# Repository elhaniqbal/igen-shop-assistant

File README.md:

<div align="center">

# HAVEN

**Automated tool dispensing and return kiosk — UBC IGEN 430 Capstone**

</div>

---

A student taps their UBC card, selects tools on a touchscreen kiosk, and the machine retrieves them — a gantry positions itself over the right carousel, rotates it to the target slot, and presents the tool at the door. Returns work in reverse. The system tracks loans, flags overdues, and sends email alerts. Everything runs in Docker on a Raspberry Pi.

This is a capstone demo. It runs end-to-end on real hardware and was built with production in mind from the start — the session mechanism, schema, network isolation, and service topology are all production-quality decisions. Getting it the rest of the way is a set of specific, well-scoped additions, not a rewrite. More on that [below](#getting-to-production).

---

## Demo

<div align="center">
  
  <br/><sub>▶ Click to watch on YouTube</sub>
</div>

---

## Architecture

```
┌──────────────────────────────────────────────────────────┐
│                 Raspberry Pi (Docker Compose)             │
│                                                          │
│  React Kiosk ──── HTTP polling ────► FastAPI Backend     │
│  (Nginx :8080)                       (Uvicorn :8000)     │
│                                      SQLite/SQLAlchemy   │
│                                            │             │
│                                       MQTT pub/sub       │
│                                            │             │
│                                  Eclipse Mosquitto       │
│                                   (1883 / WS:9001)       │
│                                            │             │
│                              ┌─────────────┴──────────┐  │
│                         Bridge sidecar      RFID sidecar │
│                         (bridge.py)        (rfid_service)│
│                              │                   │       │
└──────────────────────────────┼───────────────────┼───────┘
                               │ HTTP              │ SPI/GPIO
                        Moonraker API         MFRC522 reader
                        (:7125)
                               │ G-code macros
                            Klipper
                               │
                      BTT Octopus MAX EZ
                               │
              gantry1 / gantry2 / horiz / cake steppers
```

The frontend never touches hardware directly. It polls the backend over HTTP; the backend fires MQTT commands; the bridge translates those into Klipper G-code macros via Moonraker's HTTP API. Klipper handles all stepper control on the BTT Octopus board.

The bridge runs in one of two modes set via `BRIDGE_MODE`:
- `MOONRAKER` — real hardware via Moonraker's HTTP API
- `SIM` — software simulation with configurable timing and fail rate, no physical machine required

---

## Hardware

**Stepper axes**

- `horiz` — horizontal axis, positions the gantry over a carousel
- `gantry1`, `gantry2` — dual independent vertical axes, lifts tools in and out of slots
- `cake0`–`cake5` — one stepper per carousel, 60° per slot step

Each carousel ("cake") has 6 slots. The gantry moves horizontally to the target carousel, the vertical axes lower, the carousel rotates to the right slot, and the tool is picked up or deposited.

Vertical homing can't use Klipper's native `G28` because both gantry sides need to find their endstops independently. `vertical_home.py` handles this by jogging each side in 1600-step increments and polling Moonraker's endstop API until both trigger, then zeroing both steppers.

**Klipper macros (selected)**

```
SA_MOVE_TO_CAKE CAKE=<n>              position gantry over carousel n
SA_ROTATE_TO_SLOT CAKE=<n> SLOT=<s>   rotate carousel to absolute slot
MOVE_CAKE_CW_60 CAKE=<n>              rotate one slot clockwise
MOVE_CAKE_CCW_60 CAKE=<n>             rotate one slot counter-clockwise
SA_ROTATE_TO_DISPENSE CAKE=<n>        final alignment to dispense window
SA_MOVE_TO_DOOR                       extend gantry to door position
SA_PARK                               return to home/park
SA_HOME_HORIZONTAL                    home horizontal axis
SA_JOG_GANTRY_UP/DOWN DIST=<n>        manual jog (admin)
```

**Custom PCB — Encoder multiplexer**

<div align="center">

</div>

Each carousel has an AS5600 magnetic absolute encoder. Since all AS5600s share I2C address `0x36`, a TCA9548A multiplexer switches between them. An ESP32 reads all six, persists per-carousel zero offsets to EEPROM, and exposes a simple serial command interface.

When `ENCODER_SERIAL_ENABLED=1`, the bridge reads the angle before and after each carousel rotation and fires an alert if the measured delta is outside tolerance. Mismatches are logged and surfaced in the admin panel — it's a sanity check, not a safety gate; the operation still completes.

**NFC student card**

<div align="center">

</div>

The authentication card is a custom PCB — originally a personal side project to build a business-card-sized NFC tag. It turned out to be directly useful here: it's ISO 14443 compliant, so the MFRC522 reads it identically to any standard card. No firmware changes were needed.

---

## Sequence diagrams

<table>
<tr>
<td align="center">

<br/><sub>Dispense</sub>
</td>
<td align="center">

<br/><sub>Return</sub>
</td>
</tr>
</table>

Full diagrams with per-stage MQTT events and Moonraker calls: [`docs/system-overview.md`](docs/system-overview.md)

---

## Screenshots

<table>
<tr>
<td align="center"><br/><sub>Admin panel — manual gantry and carousel control</sub></td>
<td align="center"><br/><sub>Carousel slot state view</sub></td>
</tr>
</table>

---

## Poster

<div align="center">

</div>

---

## Stack

| | |
|---|---|
| Frontend | React 18, TypeScript, Vite, Tailwind CSS |
| Backend | Python 3.11, FastAPI, SQLAlchemy 2.0, Pydantic |
| Messaging | Eclipse Mosquitto 2, Paho |
| Database | SQLite (WAL mode) |
| Motion control | Klipper, Moonraker HTTP API |
| Firmware | Arduino/PlatformIO, ESP32, AS5600, TCA9548A |
| Infrastructure | Docker Compose, Nginx |
| Notifications | SendGrid |
| Hardware | BTT Octopus MAX EX, MFRC522 RFID, NEMA steppers |

---

## Getting started

**Prerequisites:** Docker, Docker Compose, Git

### 1. Clone and configure

```bash
git clone https://github.com/elhaniqbal/igen-shop-assistant.git
cd igen-shop-assistant
```

Create a `.env` in the repo root. Minimum to run without hardware:

```env
DATABASE_URL=sqlite:////app/data/igen.db
MQTT_BROKER=mqtt
MQTT_PORT=1883

# SIM runs without any physical hardware attached
BRIDGE_MODE=SIM

# Set to 1 to mock RFID scans in the browser
VITE_MOCK=1

# Only used in MOONRAKER mode
MOONRAKER_URL=http://host.docker.internal:7125

SENDGRID_API_KEY=
SENDGRID_FROM_EMAIL=
```

### 2. Build and start

```bash
docker compose up --build
```

| Service | URL |
|---|---|
| Kiosk | http://localhost:8080 |
| Backend API | http://localhost:5000 |
| MQTT Web UI | http://localhost:8090 |
| DB Admin | http://localhost:8083 |

The database is created automatically at `./data/igen.db` on first run.

> `5000:8000` is a dev convenience. In production, remove the port mapping — the backend is already on the `internal` Docker network and Nginx proxies it. Nothing outside the host should reach port 8000 directly.

### 3. Create the first admin user

There's no seed data. `POST /api/admin/users` has no auth guard (see [rough edges](#rough-edges)), so you can bootstrap directly:

```bash
curl -s -X POST http://localhost:5000/api/admin/users \
  -H "Content-Type: application/json" \
  -d '{
    "first_name": "Admin",
    "last_name": "User",
    "role": "admin",
    "status": "active",
    "card_id": "your-rfid-card-uid"
  }'
```

If you don't have your card UID yet, omit `card_id` and patch it in after scanning. The interactive API docs at `http://localhost:5000/docs` work for this too.

### 4. Seed inventory

Before anything can be dispensed, you need:
- **Tool models** (`POST /api/admin/tool-models`) — tool type, name, max loan hours, max quantity per user
- **Tool items** (`POST /api/admin/tool-items`) — links a physical item to a model, assigns it to a carousel slot, and registers its RFID tag

### Running against real hardware

Set `BRIDGE_MODE=MOONRAKER` and point `MOONRAKER_URL` at your Moonraker instance. The RFID sidecar needs SPI/GPIO access to the MFRC522 — the relevant device mounts are in `docker-compose.yaml`, just uncomment them.

Crowsnest (Klipper camera streaming) runs as a system service on the Pi, not in Docker. Set its port to `8091` to avoid conflicting with the kiosk on `8080`:

```conf
# /home/pi/printer_data/config/crowsnest.conf
[cam 1]
mode: ustreamer
port: 8091
device: /dev/v4l/by-id/usb-ARDUCAM_<your-camera>-video-index0
resolution: 1280x720
max_fps: 20
```

### Remote access via Tailscale

[Tailscale](https://tailscale.com) is what we use for remote access. `tailscale serve` proxies a local port to your tailnet over HTTPS; `tailscale funnel` makes it publicly reachable.

Tailnet-only (recommended for admin tools):

```bash
tailscale serve --bg http://localhost:8080          # kiosk
tailscale serve --bg --tcp 8090 tcp://localhost:8090  # MQTT Web UI
tailscale serve --bg --tcp 8083 tcp://localhost:8083  # DB Admin
tailscale serve --bg --tcp 8091 tcp://localhost:8091  # Crowsnest camera
```

Public via Funnel (for a live demo):

```bash
tailscale serve --bg http://localhost:8080
tailscale funnel --bg 443
```

Keep the MQTT broker (1883), Moonraker (7125), and the raw backend (5000) off Tailscale — none of them have auth.

---

## Rough edges

The architecture was designed with production in mind — network isolation, PostgreSQL-compatible schema, cryptographically secure sessions with revocation and role enforcement are all there. These are the specific gaps that didn't get closed before the demo:

- **Admin routes have no auth guard.** `require_admin_user()` is fully implemented in `auth.py` — it just isn't applied to the `/api/admin/*` routes yet. Anything that can reach port 5000 can create users, modify loans, or trigger hardware. Network isolation protected it for the demo.
- **No password-based admin login.** Sessions are issued after an RFID card scan — the kiosk flow is solid. There's no separate credential login for the admin web panel; access is by network position and role field.
- **Klipper positions are in step units, not millimeters.** `rotation_distance` was never configured on the `MANUAL_STEPPER` definitions. Calibration is empirical; the position numbers in the admin panel are meaningless without knowing the motor specs.
- **No crash recovery for in-progress hardware ops.** If the bridge crashes mid-dispense, `loan_requests.hw_status` stays `in_progress` and the machine's physical state is unknown. Recovery is manual: rehome, update the DB.
- **Door timeout creates unconfirmed loans.** The bridge waits 20s (`DOOR_CONFIRM_TIMEOUT_S`) for the user to confirm they've taken the tool. On timeout it marks the dispense as complete — the loan is created without `confirmed_at`.
- **Encoder mismatches don't stop operations.** A rotation that doesn't match the expected encoder delta triggers an admin alert, not a halt. The operation completes; the discrepancy is logged.

---

## Getting to production

Most of this is wiring up decisions that were already made, not new design work:

- **Apply auth guards** — `require_admin_user()` already exists in `auth.py`; add `Depends(require_admin)` to the admin routes
- **Add admin credentials** — a password field + bcrypt hash on `User`, swap the card-scan login for a form-based login on the admin panel
- **Enable cookie security flags** — set `SESSION_COOKIE_SECURE=1` in the prod env; already handled in `auth.py`
- **Swap SQLite for Postgres** — the schema uses SQLAlchemy 2.0 with standard types and proper indexes throughout; it's a `DATABASE_URL` change plus `alembic upgrade head`
- **Backend restart policy** — change `restart: no` → `restart: unless-stopped` and uncomment the healthcheck in `docker-compose.yaml`
- **Email config** — the overdue alert recipient is hardcoded in `admin.py`; pull it into an env var
- **Klipper coordinate units** — set `rotation_distance` correctly on the `MANUAL_STEPPER` definitions to get positions in mm
- **Encoder auto-correction** — the pieces are already there: the bridge reads encoder angle before and after each move, and `SA_JOG_CAKE_REL` can apply a delta; the missing piece is the measurement→correct→verify loop

---

## Repository layout

```
igen-shop-assistant/
├── services/
│   ├── backend/app/
│   │   ├── bridge.py          # MQTT → Moonraker HTTP → Klipper
│   │   ├── vertical_home.py   # Python-assisted dual-gantry homing
│   │   ├── mqtt.py            # MQTT subscriber + event dispatch
│   │   ├── models.py          # SQLAlchemy ORM
│   │   ├── auth.py            # Session tokens, revocation, role guards
│   │   ├── routers/           # FastAPI route handlers
│   │   └── usecases/          # Dispense/return orchestration
│   ├── ui/src/
│   │   ├── pages/             # Login, UserApp, AdminShell
│   │   ├── components/        # RFID panel, overlays, animations
│   │   └── lib/               # API client, endpoint map
│   └── mosquitto/
├── firmware/
│   └── encoder_mux.ino        # ESP32: 6× AS5600 via TCA9548A
├── assets/                    # Demo video, PCBs, diagrams, poster
└── docs/
    ├── model.md               # DB schema + MQTT contract
    ├── system-overview.md     # Full sequence diagrams
    └── comms-topology.md      # Service communication map
```

---

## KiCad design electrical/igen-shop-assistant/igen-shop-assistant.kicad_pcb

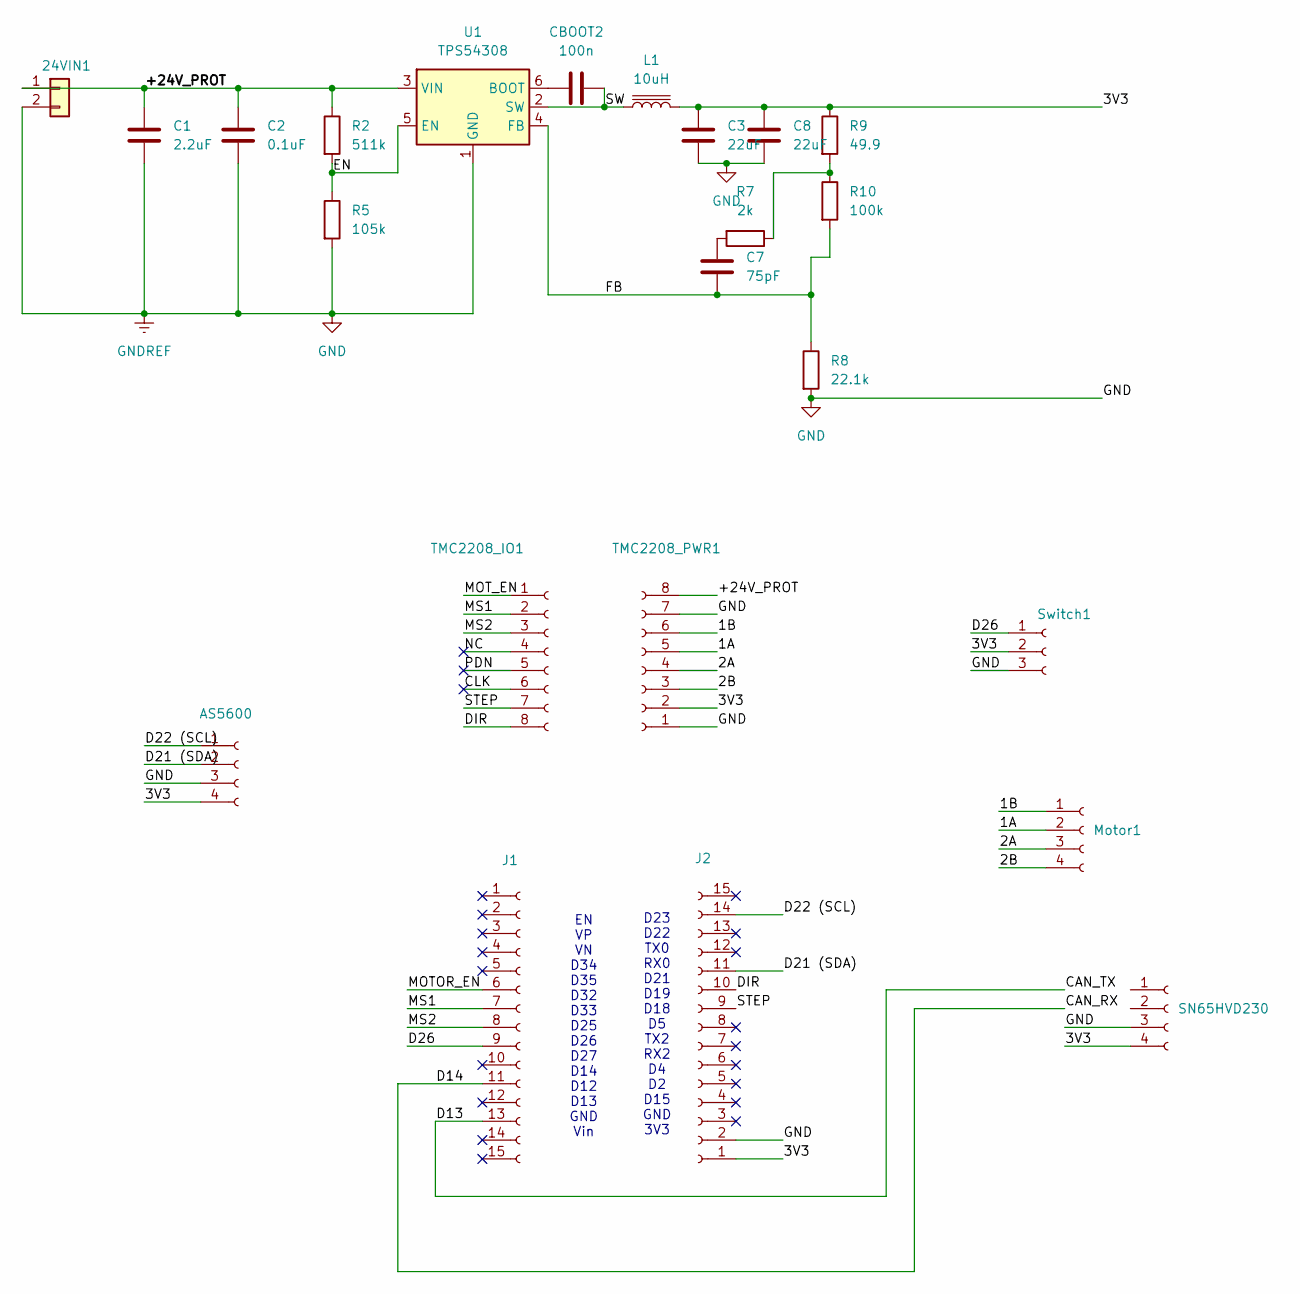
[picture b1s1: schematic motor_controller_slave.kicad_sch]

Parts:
24VIN1: Conn_01x02; TerminalBlock_Phoenix_MKDS-1,5-2_1x02_P5.00mm_Horizontal; JLCPCB Part Number C8465
AS5600: Conn_01x04_Socket; PinSocket_1x04_P2.54mm_Horizontal; JLCPCB Part Number C22373928
C1: 2.2uF; C_1210_3225Metric; JLCPCB Part Number C55151
C2: 0.1uF; C_1210_3225Metric; JLCPCB Part Number C527381
C3, C8: 22uF; C_1210_3225Metric; JLCPCB Part Number C309062
C7: 75pF; C_0603_1608Metric; JLCPCB Part Number C282074
CBOOT2: 100n; C_0805_2012Metric; JLCPCB Part Number C49678
J1, J2: Conn_01x15_Socket; PinSocket_1x15_P2.54mm_Vertical; JLCPCB Part Number C41417327
L1: 10uH; L_10.4x10.4_H4.8; JLCPCB Part Number C9185
Motor1: Conn_01x04_Socket; PinSocket_1x04_P2.54mm_Horizontal; JLCPCB Part Number C22373928
R2: 511k; R_0603_1608Metric; JLCPCB Part Number C861454
R5: 105k; R_0603_1608Metric; JLCPCB Part Number C861072
R7: 2k; R_0603_1608Metric; JLCPCB Part Number C22975
R8: 22.1k; R_0603_1608Metric; JLCPCB Part Number C25961
R9: 49.9; R_0603_1608Metric; JLCPCB Part Number C23185
R10: 100k; R_0603_1608Metric; JLCPCB Part Number C14675
SN65HVD230: Conn_01x04_Socket; PinSocket_1x04_P2.54mm_Horizontal; JLCPCB Part Number C22373928
Switch1: Conn_01x03_Socket; PinSocket_1x03_P2.54mm_Horizontal; JLCPCB Part Number C22373927
TMC2208_IO1, TMC2208_PWR1: Conn_01x08_Socket; PinSocket_1x08_P2.54mm_Vertical; JLCPCB Part Number C27438
U1: TPS54308; SOT-23-6; JLCPCB Part Number C168839

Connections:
/ESP32+CAN+TMC2208/1A: Motor1.2, TMC2208_PWR1.5
/ESP32+CAN+TMC2208/1B: Motor1.1, TMC2208_PWR1.6
/ESP32+CAN+TMC2208/2A: Motor1.3, TMC2208_PWR1.4
/ESP32+CAN+TMC2208/2B: Motor1.4, TMC2208_PWR1.3
/ESP32+CAN+TMC2208/3V3: AS5600.4, C3.1, C8.1, J2.1, L1.2, R9.1, SN65HVD230.4, Switch1.2, TMC2208_PWR1.2; also elsewhere on the board
/ESP32+CAN+TMC2208/+24V_PROT: 24VIN1.1, C1.1, C2.1, R2.1, TMC2208_PWR1.8, U1.3 (VIN)
/ESP32+CAN+TMC2208/CAN_RX: J1.11
/ESP32+CAN+TMC2208/CAN_TX: J1.13
/ESP32+CAN+TMC2208/CLK: TMC2208_IO1.6
/ESP32+CAN+TMC2208/D21 (SDA): AS5600.2, J2.11
/ESP32+CAN+TMC2208/D22 (SCL): AS5600.1, J2.14
/ESP32+CAN+TMC2208/D26: J1.9, Switch1.1; also elsewhere on the board
/ESP32+CAN+TMC2208/DIR: J2.10, TMC2208_IO1.8
/ESP32+CAN+TMC2208/EN: R2.2, R5.1, U1.5 (EN)
/ESP32+CAN+TMC2208/FB: C7.2, R8.1, R10.2, U1.4 (FB)
/ESP32+CAN+TMC2208/MOTOR_EN: J1.6
/ESP32+CAN+TMC2208/MOT_EN: TMC2208_IO1.1
/ESP32+CAN+TMC2208/MS1: J1.7, TMC2208_IO1.2
/ESP32+CAN+TMC2208/MS2: J1.8, TMC2208_IO1.3
/ESP32+CAN+TMC2208/NC: TMC2208_IO1.4
/ESP32+CAN+TMC2208/PDN: TMC2208_IO1.5
/ESP32+CAN+TMC2208/STEP: J2.9, TMC2208_IO1.7
/ESP32+CAN+TMC2208/SW: CBOOT2.2, L1.1, U1.2 (SW)
GND: 24VIN1.2, AS5600.3, C1.2, C2.2, C3.2, C8.2, J2.2, R5.2, R8.2, SN65HVD230.3, Switch1.3, TMC2208_PWR1.1, TMC2208_PWR1.7, U1.1 (GND); also elsewhere on the board
unnamed: C7.1, R7.2
unnamed: R7.1, R9.2, R10.1
unnamed: CBOOT2.1, U1.6 (BOOT)

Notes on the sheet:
EN VP VN D34 D35 D32 D33 D25 D26 D27 D14 D12 D13 GND Vin
D23 D22 TX0 RX0 D21 D19 D18 D5 TX2 RX2 D4 D2 D15 GND 3V3

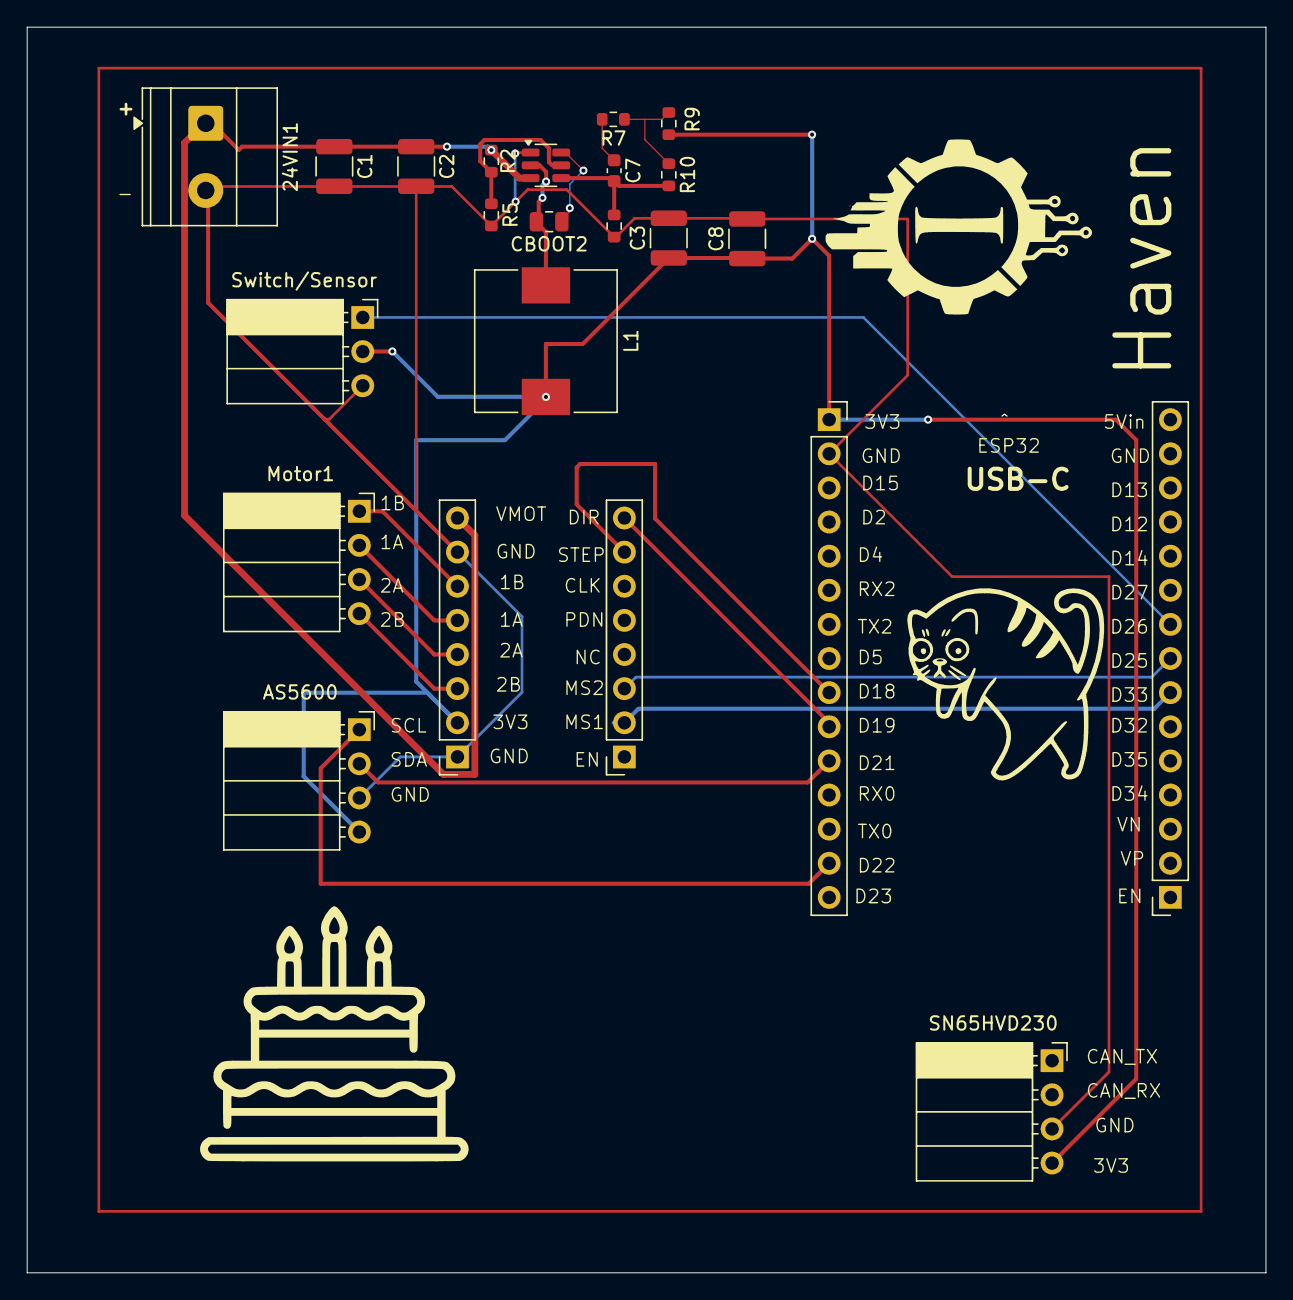
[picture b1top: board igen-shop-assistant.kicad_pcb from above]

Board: 2 copper layers, 92.2 x 92.7 mm, 23 parts (0 on the bottom side), 20 nets.

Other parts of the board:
Switch/Sensor: Conn_01x03_Socket; PinSocket_1x03_P2.54mm_Horizontal

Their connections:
/ESP32+CAN+TMC2208/3V3: Switch/Sensor.2; also elsewhere on the board
/ESP32+CAN+TMC2208/D26: Switch/Sensor.1; also elsewhere on the board
GND: Switch/Sensor.3; also elsewhere on the board

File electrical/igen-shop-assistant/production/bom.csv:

Designator,Footprint,Quantity,Value,LCSC Part #
24VIN1,"TerminalBlock_Phoenix_MKDS-1,5-2_1x02_P5.00mm_Horizontal",1,Conn_01x02,C8465
"AS5600, MOTOR1, SN65HVD230",PinSocket_1x04_P2.54mm_Horizontal,3,Conn_01x04_Socket,C22373928
C1,1210,1,2.2uF,C55151
C2,1210,1,0.1uF,C527381
"C3, C8",1210,2,22uF,C309062
C7,0603,1,75pF,C282074
CBOOT2,0805,1,100n,C49678
"J1, J2",PinSocket_1x15_P2.54mm_Vertical,2,Conn_01x15_Socket,C41417327
L1,L_10.4x10.4_H4.8,1,10uH,C9185
R10,0603,1,100k,C14675
R2,0603,1,511k,C861454
R5,0603,1,105k,C861072
R7,0603,1,2k,C22975
R8,0603,1,22.1k,C25961
R9,0603,1,49.9,C23185
SWITCH/SENSOR,PinSocket_1x03_P2.54mm_Horizontal,1,Conn_01x03_Socket,C22373927
"TMC2208_IO1, TMC2208_PWR1",PinSocket_1x08_P2.54mm_Vertical,2,Conn_01x08_Socket,C27438
U1,SOT-23-6,1,TPS54308,C168839

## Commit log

2025-09-17 Starter Code Scaffold
2025-09-24 Initial BOM
2025-10-07 CAN Test
2025-10-07 added test runner workflow
2025-10-14 updates as of 14th oct 1:22am
2025-10-15 added wheel logic static test site and updated docker compose
2025-10-15 updated deploy workflow
2025-10-15 fix deploy.yaml
2025-10-15 test updates
2025-10-26 updated BOM
2025-12-06 motor-test
2025-12-06 Added electrical schematic
2025-12-18 some changes [unfinished]
2025-12-23 test commit
2025-12-24 some small fixes
2025-12-24 some more bugs, updates and features
2025-12-24 Create cake storage logic file in C++ and corresponding unit test script
2025-12-24 Created README on how to run firmware tests
2025-12-25 some updates
2025-12-27 Fixed status display to show NOT_AVAILABLE when active flag set to false
2025-12-28 changed card tapping animation on login page
2025-12-28 Fixed bugs related to login with RFID
2026-01-12 Moved Dockerfile.rfid into app directory, modified docker file to enable GPIO and SPI access, modified rfid_service.py script to match expected data schema when publishing to MQTT topic
2026-03-11 camera config
2026-03-14 added btt-config
2026-03-16 some refinements and additional macros
2026-03-16 Some basic manual control frontend components
2026-03-23 some frontend updates
2026-03-24 update checkpoint, will continue later
2026-03-28 checkpoint, more bug fixes pending
2026-03-30 checkout, still some nasty bugs to wipe out
2026-04-02 patches, updated as of Apr 2
2026-04-03 updated stepper config
2026-04-03 patched admin.py
2026-04-03 updated pyproject.toml
2026-04-03 added brandon's changes
2026-04-03 inline .cfg file editor
2026-04-04 current rpi state
2026-04-08 more updates
2026-06-06 documentation cleanup and new readme
2026-06-07 clean up job v1
